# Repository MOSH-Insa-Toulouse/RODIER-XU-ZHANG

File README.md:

# ReadMe file for project KiCAD
Some kicad files to print the PCB of a gas sensor Arduino UNO shield.

## Authors: Nicolas RODIER, Hao XU and Guangjie ZHANG from 2018-2019 5th year Innovative Smart System at Insa Toulouse

## Credits
* This kicad project was inspired by Jeremie Grisolia’s work (Université de Toulouse LPCNO/INSA, jeremie.grisolia@insa-toulouse.fr): 
Un «smart device» à base de capteur de gaz à nanoparticules 
* The GROVE footprint was inspired by ShrodingersGat’s work, found on https://github.com/KiCad/Connectors.pretty.
* This project would not have been possible without Arnaud Biganzoli’s course (INSA Toulouse) and the [“Getting started” Kicad documentation](http://docs.kicad-pcb.org/master/nl/getting_started_in_kicad.pdf).

## Aim: 
In this project, we aimed to design the architecture of a PCB containing a gas sensor to be integrated on a Arduino UNO card. 

## Features:
* A TO5 connector compliant gas sensor (cf. Rsensor on figure 1). 
* A grove connector compliant gas sensor for reference.
* LoRa communication system.
* Noise shielded devices using a low pass filter (C1, C4 and C2, see fig1).
* An AOP (LTC1050)
* 3x100kF and 1xµF condensators.
* 1x220Ω, 2x1kΩ, 1x10kΩ, 2x100kΩ resistors
* Connected to an arduino board.

## Process:
### Eeschema
To begin with, we designed the following circuit on Eeschema:

![Figure 1:  Circuit architecture] (/GazSensor-Rodier&Xu/images/Figure1.png)
Figure 1:  Circuit architecture

In this diagram, we can see clearly there are some resistances, capacitances and a LTC1050 model (cf. Features AOP). In fact, in the practice course KiCAD, we have realized a LTC1050 symbol and saved it in the library, so here in the Eeschema file we can use it directly. 

But for using the gas sensor, we put a TO5 element in the place of Rsensor. In order to integrate our PCB card with the element RN2483, we also added a connector with 8 pins.

Then we added the Arduino UNO card and connect its pins with other parts in this diagram. All the pins which we don’t connect, we added a symbole “non connected” to avoid errors while compiling. 

Finally, we draw a grove connector symbol in order to plug the reference gas sensor. The final structure of Eeschema file is shown in the figure 2.

Figure 2: Eeschema file

After having finished that, we chose the correct footprint component. If needed, import one. We chose the footprint as followed:

Figure 3 : Footprint selection

Finally, we produce the netlist, so we can import the footprint on the next tool: PCBnew.

### PCBnew
PCBnew is a powerful tool allowing you to display every component in 2 or 3D and design your pcb. Import the netlist and arrange the component so the “chevelus” (the white line) do not cross. Then, change the track dimension to their appropriate size as described on the next picture:

Figure 4: Appropriate size for lines

Draw the tracks in order to connect every component between each other. As there are no automatic arrangement features in kicad, you will probably need to do it a few times. TIP: use the “Reglage du routeur interactif” (Ctrl+,) feature. When you are done, fill the pcb and plot the Gerber plot and drill files to be able to print your brand new pcb card.

### Gerber
Examine carefully your files. If everything is fine, you can send it to your favorite 3D printer !

## Additional remarks
The system could be fully shielded using a digital filter directly on the microprocessor. Finally, we could add a LCD screen in order to visually monitor the gas sensor activity. 

## References
* [UF Microcontrolleurs et open-source hardware](https://moodle.insa-toulouse.fr/course/view.php?id=494)
* [The impedance adaptation circuit](https://moodle.insa-toulouse.fr/pluginfile.php/70769/mod_resource/content/1/The_impedance_adaptation_circuit.pdf)
* [Datasheet TO5](https://docs-emea.rs-online.com/webdocs/0f9e/0900766b80f9e51c.pdf)
* [Datasheet RN2483](http://ww1.microchip.com/downloads/en/DeviceDoc/50002346C.pdf)

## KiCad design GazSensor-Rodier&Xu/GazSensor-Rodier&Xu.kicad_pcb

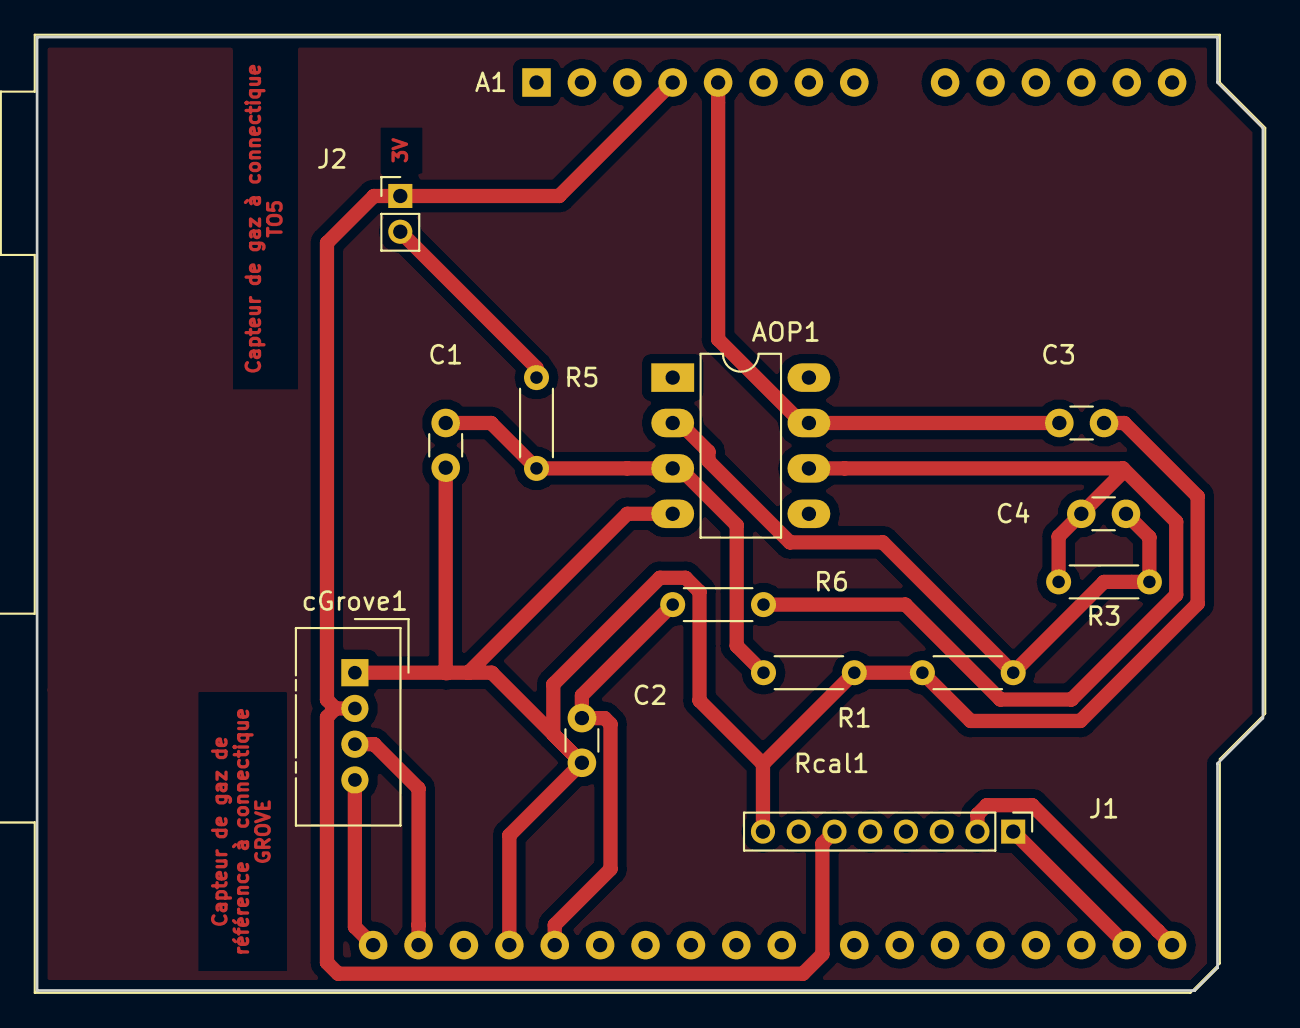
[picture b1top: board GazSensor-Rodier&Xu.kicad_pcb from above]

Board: 2 copper layers, 68.6 x 53.3 mm, 14 parts (0 on the bottom side), 12 nets.

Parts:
A1: Arduino Uno; Arduino_UNO_R3
AOP1: LTC1050; DIP-8_W7.62mm_LongPads
C1, C2, C3: 100n; C_Disc_D3.0mm_W1.6mm_P2.50mm
C4: 1u; C_Disc_D3.0mm_W1.6mm_P2.50mm
J1: Conn_01x08_Female; PinHeader_1x08_P2.00mm_Vertical
J2: Conn_01x02_Female; PinHeader_1x02_P2.00mm_Vertical
R1, R3: 100k; R_Axial_DIN0204_L3.6mm_D1.6mm_P5.08mm_Horizontal
R5: 10k; R_Axial_DIN0204_L3.6mm_D1.6mm_P5.08mm_Horizontal
R6: 1k; R_Axial_DIN0204_L3.6mm_D1.6mm_P5.08mm_Horizontal
Rcal1: 5k; R_Axial_DIN0204_L3.6mm_D1.6mm_P5.08mm_Horizontal
cGrove1: connectiqueGrove; NS-Tech_Grove_1x04_P2mm_Vertical

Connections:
unnamed: AOP1.2, C4.2, R3.1, Rcal1.1
unnamed: AOP1.3, C1.1, R1.2, R5.1
unnamed: AOP1.6, C4.1, R3.2, R6.1
unnamed: J2.2, R5.2
arduino: A1.28, C2.1, R6.2
arduino3v: A1.4, J1.6, J2.1, cGrove1.2
arduino5v: A1.5, AOP1.7, C3.2
arduinoRx: A1.15, J1.2
arduinoSCL: A1.32, cGrove1.4
arduinoSDA: A1.31, cGrove1.3
arduinoTx: A1.16, J1.1
arduinognd: A1.29, AOP1.4, C1.2, C2.2, C3.1, J1.8, R1.1, Rcal1.2, cGrove1.1
